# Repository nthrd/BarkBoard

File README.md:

BarkBoard
=========

BarkBoard Audio DSP Board for the BeagleBone Black

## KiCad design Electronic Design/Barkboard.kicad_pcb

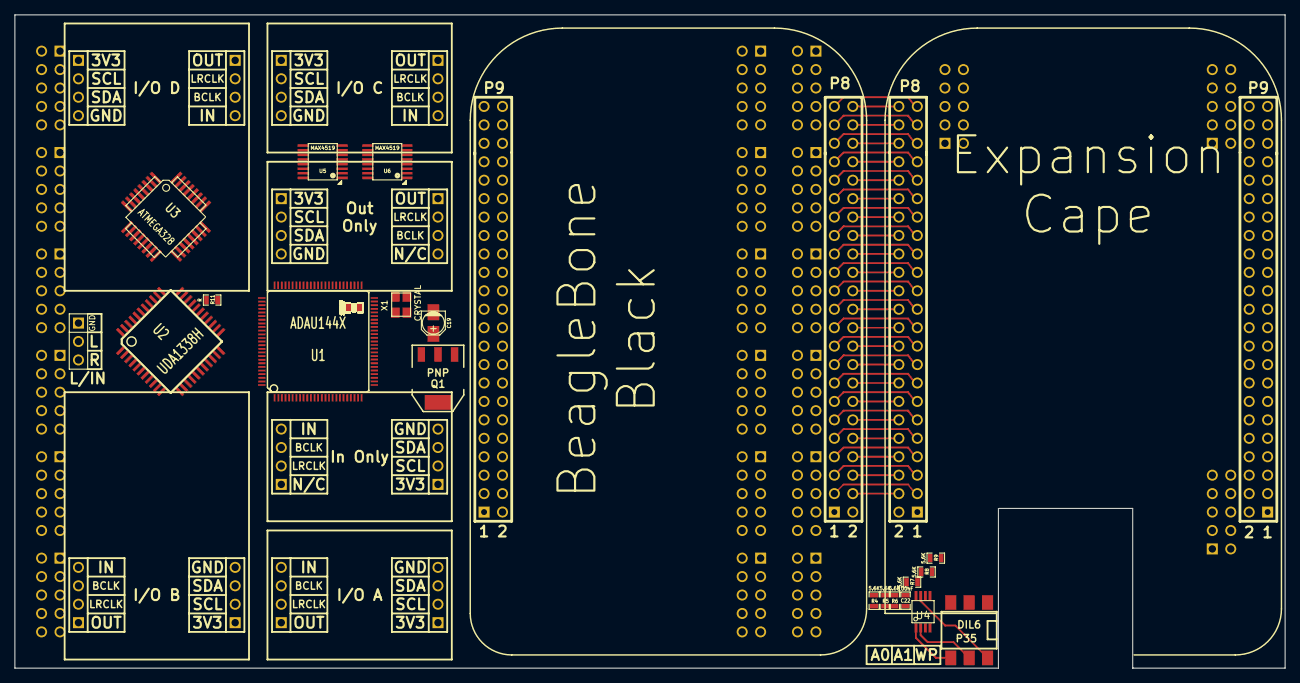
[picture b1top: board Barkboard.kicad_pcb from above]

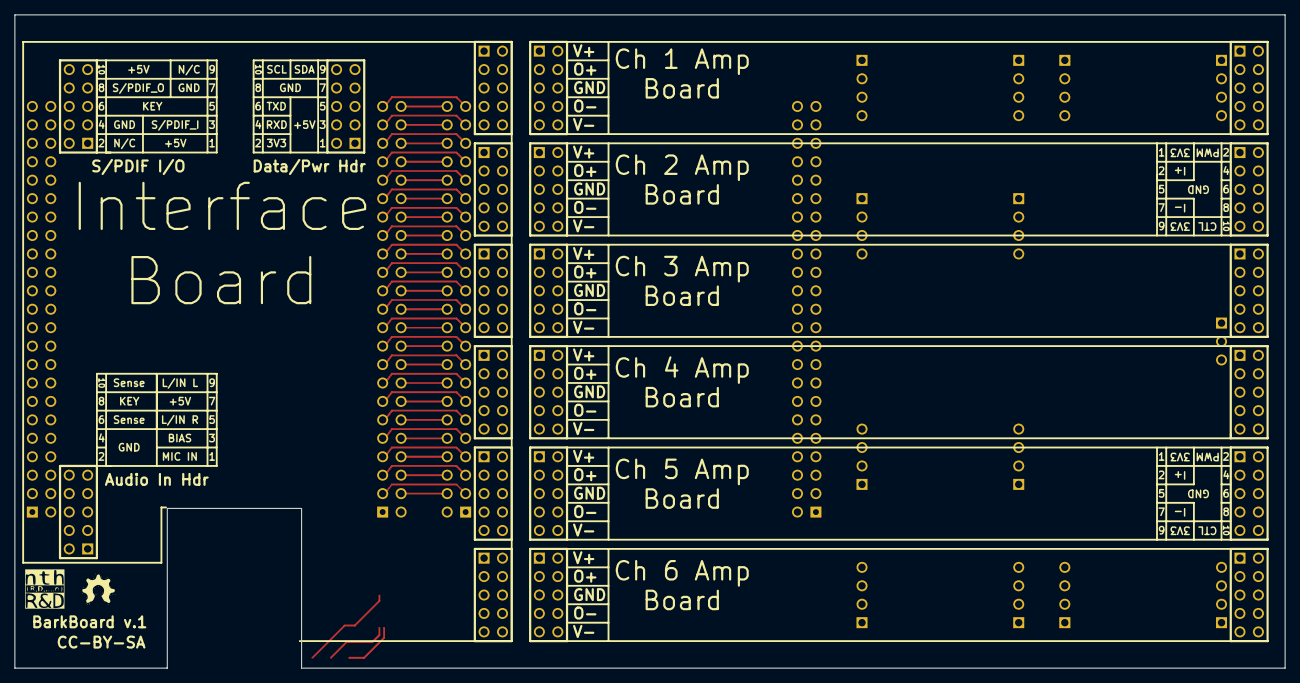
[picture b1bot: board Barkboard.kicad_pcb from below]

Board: 4 copper layers, 175.0 x 90.0 mm, 79 parts (21 on the bottom side), 197 nets.

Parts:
C1: 33nF; SM0603_Capa
C2: 1.8nF; SM0603_Capa
C3, C4, C5, C6, C7, C8, C9, C10, C11, C12, C13, C14, C15, C16, C17, C18, C22: 100nF; SM0603_Capa
C19: 10uF; c_elec_3x5.3
C20, C21: 22pF; SM0603_Capa
P1: Bone_P8; BONE_HDR_FLIP
P2: Bone_P9; BONE_HDR_FLIP
P3: Cape_P8; PIN_ARRAY_23X2
P4: Cape_P9; PIN_ARRAY_23X2
P5, P6, P7, P8, P9, P10, P11, P12, P13, P14, P15, P16, P21, P22, P23, P24, P25, P26, P36, P37, P38: CONN_5X2; PIN_ARRAY_5x2
P17: IODA; PIN_ARRAY_4x1
P18: IOPA; PIN_ARRAY_4x1
P19: IODB; PIN_ARRAY_4x1
P20: IOPB; PIN_ARRAY_4x1
P27: IODC; PIN_ARRAY_4x1
P28: IOPC; PIN_ARRAY_4x1
P29: IODD; PIN_ARRAY_4x1
P30: IOPD; PIN_ARRAY_4x1
P31: IP; PIN_ARRAY_4x1
P32: ID; PIN_ARRAY_4x1
P33: OP; PIN_ARRAY_4x1
P34: OD; PIN_ARRAY_4x1
P35: DIL6; 6DIPCMS
P39: CONN_3; PIN_ARRAY_3X1
Q1: PNP; SOT223
R1: 1.5K; SM0603_Resistor
R2: 10K; SM0603_Resistor
R3: 100; SM0603_Resistor
R4, R5, R6, R7, R8, R9: 5.6K; SM0603_Resistor
R11: R; SM0603_Resistor
U1: ADAU144X; TQFP_100
U2: UDA1338H; TQFP44
U3: ATMEGA328; TQFP32
U4: 24C256; SSOP8
U5, U6: MAX4519; qsop-16
X1: CRYSTAL; crystal_FA238-TSX3225

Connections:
3V3: C2.1, C3.1, C5.1, C6.1, C8.1, C10.1, C11.1, C13.1, C14.1, C16.1, C18.1, P18.1, P20.1, P21.1, P21.9, P22.1, P22.9, P23.1, P23.9, P24.1, P24.9, P25.1, P25.9, P26.1, P26.9, P28.1, P30.1, P31.1, P33.1, P38.2, Q1.1, R1.1, R11.1, U1.2, U1.14, U1.27, U1.39, U1.44, U1.49, U1.52, U1.63, U1.77, U1.89, U2.5, U2.9, U2.29, U2.37, U5.2, U5.14, U6.2, U6.14
+1.8V: C4.1, C7.1, C9.1, C12.1, C15.1, C17.1, C19.1, Q1.3, U1.25, U1.37, U1.50, U1.75, U1.87, U1.100
+5V: P2.5, P2.6, P4.5, P4.6, P36.1, P36.10, P37.7, P38.1, P38.3, P38.5
/AD1: U1.5, U2.13
/AD2: U1.8, U2.12
/ADBC: U1.9, U2.14
/ADLR: U1.10, U2.15
/ADV: U1.11, U2.16
/ADVBC: U1.12, U2.17
/ADVLR: U1.15, U2.18
/AD_RESET: U1.54, U3.23
/AT_RX: U3.30, U5.10, U6.4
/AT_TX: U3.31, U5.4, U6.10
/Amplifier and Interface Connectors/C1_CTL: P21.10, U3.32
/Amplifier and Interface Connectors/C1_I+: P21.3, U2.31
/Amplifier and Interface Connectors/C1_I-: P21.7, U2.32
/Amplifier and Interface Connectors/C1_O+: P5.3, P5.4, P11.3, P11.4
/Amplifier and Interface Connectors/C1_O-: P5.7, P5.8, P11.7, P11.8
/Amplifier and Interface Connectors/C1_PWM: P21.2, U3.1
/Amplifier and Interface Connectors/C1_V+: P5.1, P5.2, P11.1, P11.2
/Amplifier and Interface Connectors/C1_V-: P5.9, P5.10, P11.9, P11.10
/Amplifier and Interface Connectors/C2_CTL: P22.10, U3.2
/Amplifier and Interface Connectors/C2_I+: P22.3, U2.33
/Amplifier and Interface Connectors/C2_I-: P22.7, U2.34
/Amplifier and Interface Connectors/C2_O+: P6.3, P6.4, P12.3, P12.4
/Amplifier and Interface Connectors/C2_O-: P6.7, P6.8, P12.7, P12.8
/Amplifier and Interface Connectors/C2_PWM: P22.2, U3.9
/Amplifier and Interface Connectors/C2_V+: P6.1, P6.2, P12.1, P12.2
/Amplifier and Interface Connectors/C2_V-: P6.9, P6.10, P12.9, P12.10
/Amplifier and Interface Connectors/C3_CTL: P23.10, U3.11
/Amplifier and Interface Connectors/C3_I+: P23.3, U2.35
/Amplifier and Interface Connectors/C3_I-: P23.7, U2.36
/Amplifier and Interface Connectors/C3_O+: P7.3, P7.4, P13.3, P13.4
/Amplifier and Interface Connectors/C3_O-: P7.7, P7.8, P13.7, P13.8
/Amplifier and Interface Connectors/C3_PWM: P23.2, U3.10
/Amplifier and Interface Connectors/C3_V+: P7.1, P7.2, P13.1, P13.2
/Amplifier and Interface Connectors/C3_V-: P7.9, P7.10, P13.9, P13.10
/Amplifier and Interface Connectors/C4_CTL: P24.10, U3.12
/Amplifier and Interface Connectors/C4_I+: P24.3, U2.38
/Amplifier and Interface Connectors/C4_I-: P24.7, U2.39
/Amplifier and Interface Connectors/C4_O+: P8.3, P8.4, P14.3, P14.4
/Amplifier and Interface Connectors/C4_O-: P8.7, P8.8, P14.7, P14.8
/Amplifier and Interface Connectors/C4_PWM: P24.2, U3.13
/Amplifier and Interface Connectors/C4_V+: P8.1, P8.2, P14.1, P14.2
/Amplifier and Interface Connectors/C4_V-: P8.9, P8.10, P14.9, P14.10
/Amplifier and Interface Connectors/C5_CTL: P25.10, U3.16
/Amplifier and Interface Connectors/C5_I+: P25.3, U2.41
/Amplifier and Interface Connectors/C5_I-: P25.7, U2.42
/Amplifier and Interface Connectors/C5_O+: P9.3, P9.4, P15.3, P15.4
/Amplifier and Interface Connectors/C5_O-: P9.7, P9.8, P15.7, P15.8
/Amplifier and Interface Connectors/C5_PWM: P25.2, U3.14
/Amplifier and Interface Connectors/C5_V+: P9.1, P9.2, P15.1, P15.2
/Amplifier and Interface Connectors/C5_V-: P9.9, P9.10, P15.9, P15.10
/Amplifier and Interface Connectors/C6_CTL: P26.10, U3.17
/Amplifier and Interface Connectors/C6_I+: P26.3, U2.43
/Amplifier and Interface Connectors/C6_I-: P26.7, U2.44
/Amplifier and Interface Connectors/C6_O+: P10.3, P10.4, P16.3, P16.4
/Amplifier and Interface Connectors/C6_O-: P10.7, P10.8, P16.7, P16.8
/Amplifier and Interface Connectors/C6_PWM: P26.2, U3.15
/Amplifier and Interface Connectors/C6_V+: P10.1, P10.2, P16.1, P16.2
/Amplifier and Interface Connectors/C6_V-: P10.9, P10.10, P16.9, P16.10
/Amplifier and Interface Connectors/LineIn_L: P37.9, U2.6
/Amplifier and Interface Connectors/LineIn_R: P37.5, U2.8
/Amplifier and Interface Connectors/MIC: P37.1, U2.10
/Amplifier and Interface Connectors/SPDIF_IN: P36.3, U1.46
/Amplifier and Interface Connectors/SPDIF_OUT: P36.8, U1.47
/Amplifier and Interface Connectors/UART_RX: P38.4, U6.11
/Amplifier and Interface Connectors/UART_TX: P38.6, U5.11
/BeagleBone and Cape/3V3_exp: C22.1, P2.3, P2.4, P4.3, P4.4, R4.1, R5.1, R6.1, R7.1, R8.1, R9.1, U4.8
/BeagleBone and Cape/5V_SYS: P2.7, P2.8, P4.7, P4.8
/BeagleBone and Cape/AIN0: P2.39, P4.39
/BeagleBone and Cape/AIN1: P2.40, P4.40
/BeagleBone and Cape/AIN2: P2.37, P4.37
/BeagleBone and Cape/AIN3: P2.38, P4.38
/BeagleBone and Cape/AIN4: P2.33, P4.33
/BeagleBone and Cape/AIN5: P2.36, P4.36
/BeagleBone and Cape/AIN6: P2.35, P4.35
/BeagleBone and Cape/CLKOUT2: P2.41, P4.41
/BeagleBone and Cape/EHRPWM1A: P2.14, P4.14
/BeagleBone and Cape/EHRPWM1B: P2.16, P4.16
/BeagleBone and Cape/EHRPWM2A: P1.19, P3.19
/BeagleBone and Cape/EHRPWM2B: P1.13, P3.13
/BeagleBone and Cape/GNDA_ADC: P2.34, P4.34
/BeagleBone and Cape/GPIO0_7: P2.42, P4.42
/BeagleBone and Cape/GPIO0_26: P1.14, P3.14
/BeagleBone and Cape/GPIO1_0: P1.25, P3.25
/BeagleBone and Cape/GPIO1_1: P1.24, P3.24
/BeagleBone and Cape/GPIO1_2: P1.5, P3.5
/BeagleBone and Cape/GPIO1_3: P1.6, P3.6
/BeagleBone and Cape/GPIO1_4: P1.23, P3.23
/BeagleBone and Cape/GPIO1_5: P1.22, P3.22
/BeagleBone and Cape/GPIO1_6: P1.3, P3.3
/BeagleBone and Cape/GPIO1_7: P1.4, P3.4
/BeagleBone and Cape/GPIO1_12: P1.12, P3.12
/BeagleBone and Cape/GPIO1_13: P1.11, P3.11
/BeagleBone and Cape/GPIO1_14: P1.16, P3.16
/BeagleBone and Cape/GPIO1_15: P1.15, P3.15
/BeagleBone and Cape/GPIO1_16: P2.15, P4.15
/BeagleBone and Cape/GPIO1_17: P2.23, P4.23
/BeagleBone and Cape/GPIO1_27: P1.17, P3.17
/BeagleBone and Cape/GPIO1_28: P2.12, P4.12
/BeagleBone and Cape/GPIO1_29: P1.26, P3.26
/BeagleBone and Cape/GPIO1_30: P1.21, P3.21
/BeagleBone and Cape/GPIO1_31: P1.20, P3.20
/BeagleBone and Cape/GPIO2_1: P1.18, P3.18
/BeagleBone and Cape/GPIO2_6: P1.45, P3.45
/BeagleBone and Cape/GPIO2_7: P1.46, P3.46
/BeagleBone and Cape/GPIO2_8: P1.43, P3.43
/BeagleBone and Cape/GPIO2_9: P1.44, P3.44
/BeagleBone and Cape/GPIO2_10: P1.41, P3.41
/BeagleBone and Cape/GPIO2_11: P1.42, P3.42
/BeagleBone and Cape/GPIO2_12: P1.39, P3.39
/BeagleBone and Cape/GPIO2_13: P1.40, P3.40
/BeagleBone and Cape/GPIO2_22: P1.27, P3.27
/BeagleBone and Cape/GPIO2_23: P1.29, P3.29
/BeagleBone and Cape/GPIO2_24: P1.28, P3.28
/BeagleBone and Cape/GPIO2_25: P1.30, P3.30
/BeagleBone and Cape/GPIO3_19: P2.27, U1.90
/BeagleBone and Cape/GPIO3_21: P2.25, P4.25
/BeagleBone and Cape/ID_ADD0: P35.4, R4.2, U4.1
/BeagleBone and Cape/ID_ADD1: P35.5, R5.2, U4.2
/BeagleBone and Cape/ID_SCL: P2.19, P4.19, R8.2, U4.6
/BeagleBone and Cape/ID_SDA: P2.20, P4.20, R9.2, U4.5
/BeagleBone and Cape/PWR_BUT: P2.9, P4.9
/BeagleBone and Cape/SPI1_CS: P2.28, U1.84
/BeagleBone and Cape/SPI1_D0: P2.29, U1.86
/BeagleBone and Cape/SPI1_D1: P2.30, P4.30
/BeagleBone and Cape/SPI1_SCLK: P2.31, U1.85
/BeagleBone and Cape/SYS_RESETn: P2.10, P4.10
/BeagleBone and Cape/TIEMR5: P1.9, P3.9
/BeagleBone and Cape/TIMER4: P1.7, P3.7
/BeagleBone and Cape/TIMER6: P1.10, P3.10
/BeagleBone and Cape/TIMER7: P1.8, P3.8
/BeagleBone and Cape/UART1_RXD: P2.26, P4.26, U6.5
/BeagleBone and Cape/UART1_TXD: P2.24, P4.24, U5.5
/BeagleBone and Cape/UART2_RXD: P2.22, P4.22
/BeagleBone and Cape/UART2_TXD: P2.21, P4.21
/BeagleBone and Cape/UART3_CTSN: P1.36, P3.36
/BeagleBone and Cape/UART3_RTSN: P1.34, P3.34
/BeagleBone and Cape/UART4_CTSN: P1.35, P3.35
/BeagleBone and Cape/UART4_RTSN: P1.33, P3.33
/BeagleBone and Cape/UART4_RXD: P2.11, P4.11
/BeagleBone and Cape/UART4_TXD: P2.13, P4.13
/BeagleBone and Cape/UART5_CTSN: P1.31, P3.31
/BeagleBone and Cape/UART5_RTSN: P1.32, P3.32
/BeagleBone and Cape/UART5_RXD: P1.38, P3.38
/BeagleBone and Cape/UART5_TXD: P1.37, P3.37
/BeagleBone and Cape/VDD_ADC: P2.32, P4.32
/BeagleBone and Cape/WP: P35.6, R7.2, U4.7
/DA12: U1.69, U2.25
/DA34: U1.66, U2.26
/DA56: U1.61, U2.27
/DABC: U1.64, U2.24
/DALR: U1.65, U2.23
/IBC: P32.3, U1.3
/II: P32.4, U1.99
/ILR: P32.2, U1.4
/IOABC: P17.3, U1.96
/IOAI: P17.4, U1.95
/IOALR: P17.2, U1.97
/IOAO: P17.1, U1.98
/IOBBC: P19.3, U1.92
/IOBI: P19.4, U1.91
/IOBLR: P19.2, U1.93
/IOBO: P19.1, U1.94
/IOCBC: P27.3, U1.74
/IOCI: P27.4, U1.73
/IOCLR: P27.2, U1.78
/IOCO: P27.1, U1.79
/IODBC: P29.3, U1.81
/IODI: P29.4, U1.80
/IODLR: P29.2, U1.82
/IODO: P29.1, U1.83
/MP8: U1.19, U5.1, U6.1
/MP9: U1.18, U5.16, U6.16
/MP10: U1.17, U3.29
/MP11: U1.16, U2.20
/MSTR_CLK: U1.53, U2.19
/OBC: P34.3, U1.70
/OLR: P34.2, U1.71
/OO: P34.1, U1.72
/PFILT: C1.2, C2.2, U1.43
/VDRIVE: Q1.2, U1.40
/XI: C20.1, U1.42, X1.2
/XO1: R3.1, U1.41
/XO2: C21.1, R3.2, X1.1
GND: C3.2, C4.2, C5.2, C6.2, C7.2, C8.2, C9.2, C10.2, C11.2, C12.2, C13.2, C14.2, C15.2, C16.2, C17.2, C18.2, C19.2, C20.2, C21.2, C22.2, P1.1, P1.2, P2.1, P2.2, P2.43, P2.44, P2.45, P2.46, P3.1, P3.2, P4.1, P4.2, P4.43, P4.44, P4.45, P4.46, P5.5, P5.6, P6.5, P6.6, P7.5, P7.6, P8.5, P8.6, P9.5, P9.6, P10.5, P10.6, P11.5, P11.6, P12.5, P12.6, P13.5, P13.6, P14.5, P14.6, P15.5, P15.6, P16.5, P16.6, P18.4, P20.4, P21.4, P21.5, P21.6, P21.8, P22.4, P22.5, P22.6, P22.8, P23.4, P23.5, P23.6, P23.8, P24.4, P24.5, P24.6, P24.8, P25.4, P25.5, P25.6, P25.8, P26.4, P26.5, P26.6, P26.8, P28.4, P30.4, P31.4, P33.4, P35.1, P35.2, P35.3, P36.4, P36.7, P37.2, P37.4, P38.7, P38.8, P39.1, R2.1, U1.1, U1.13, U1.20, U1.21, U1.24, U1.26, U1.28, U1.38, U1.45, U1.48, U1.51, U1.62, U1.76, U1.88, U2.3, U2.7, U2.11, U2.28, U2.40, U3.3, U3.5, U3.21, U4.4, U5.3, U5.13, U6.3, U6.13
unnamed: R2.2, U1.31
unnamed: C1.1, R1.2
unnamed: R11.2, U2.30
unnamed: P39.2, U2.2
unnamed: P39.3, U2.4
unnamed: U5.6, U5.9
unnamed: U6.6, U6.9
unnamed: R6.2, U4.3
SCL: P2.17, P4.17, P18.2, P20.2, P28.2, P30.2, P31.2, P33.2, P38.10, U1.22, U2.21, U3.28
SDA: P2.18, P4.18, P18.3, P20.3, P28.3, P30.3, P31.3, P33.3, P38.9, U1.23, U2.22, U3.27

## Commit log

2014-08-10 Fixed end of file new line
2014-08-10 Better Readme
2014-08-10 Minor changes to fix markdown

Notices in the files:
Electronic Design/Barkboard.kicad_pcb:
CC-BY-SA
